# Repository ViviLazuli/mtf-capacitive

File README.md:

# MtF122 Capacitive Conversion PCB for IBM Model M 122-key Keyboards

### Rev. 2 / Rev. B

This version is in prototyping phase. However, it does function.

It has only been tested with a late thin-bezeled variant of the M122. The screw holes have a tight fit and may require widening and more clearance around them for traces.
!The screw holes may not be in the correct positions for other M122 variants!

Capacitive pad measurements are taken from i$/idollar's FSSK and FEXT PCB designs, which I believe are directly measured from the original Model F PCBs.

The PCB thickness should be 0.6mm. This is thin enough to allow the board to flex into shape without preforming it with heat and duct tape (which I couldn't make work anyway).

Standard glossy soldermask is probably the best choice. JLCPCB has had issues with wear on their black soldermask before. They have changed the formula, but a standard green/red/blue/yellow/purple/white/etc. glossy solder mask is probaby the safest bet for keyswitch wear resistance.
Higher wear resistance might also be achieved by coating the front of the capacitive pads in silkscreen, as silkscreen is an extra layer of epoxy. I am unsure how this will affect keyfeel or actuation, however.

There is a bullseye circle on the front of the board. This is for drilling a hole for a trackpoint module. There are redundant traces to allow for safer drilling at this location, but this functionality has not been tested!

The diameter of the copper around the connecting pads could be to be enlarged. They are too fragile and I had one rip out when disconnecting a mill-max pin header connector (fortunately it was just a redundant ground).

For connecting the board to an xwhatsit or other controller, I would recommend 3M 8132/06 100, which has the correct pitch for this board and xwhatsit:
https://www.digikey.com/en/products/detail/3m/8132-06-100/7809902

The key matrix of the PCB is reverse-engineered from photos of original F122 PCBs and should be exactly the same. The connector is likely in a slightly different position though.

The screw hole placement was prototyped with paper by printing an SVG output of the board edge cuts and drill holes on multiple sheets of paper, pasting them together, cutting out the paper 'PCB', and hole punching the drill hole locations. A few iterations of this paper prototyping method allowed me to test hole locations and board fitment against the barrel plate without having to make an entire PCB first.

I did not clad the steel backplate in tape before mounting the PCB. The solder mask should provide adequate isolation. Just make sure the steel is clean and there are no burrs/jagged edges that could scrape the PCB.

Please read LICENSE.txt for the full MIT License.

Some photos are here for reverse-engineering reference only and are not mine nor included under the license.

| Authors |
|-|
| ViviLazuli |
| Razerban |

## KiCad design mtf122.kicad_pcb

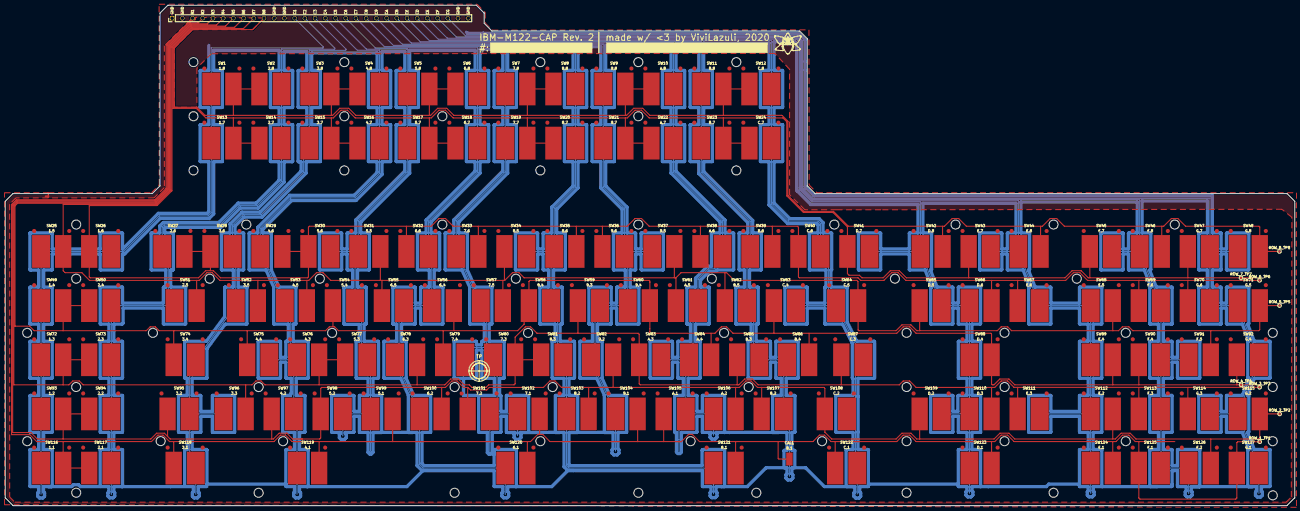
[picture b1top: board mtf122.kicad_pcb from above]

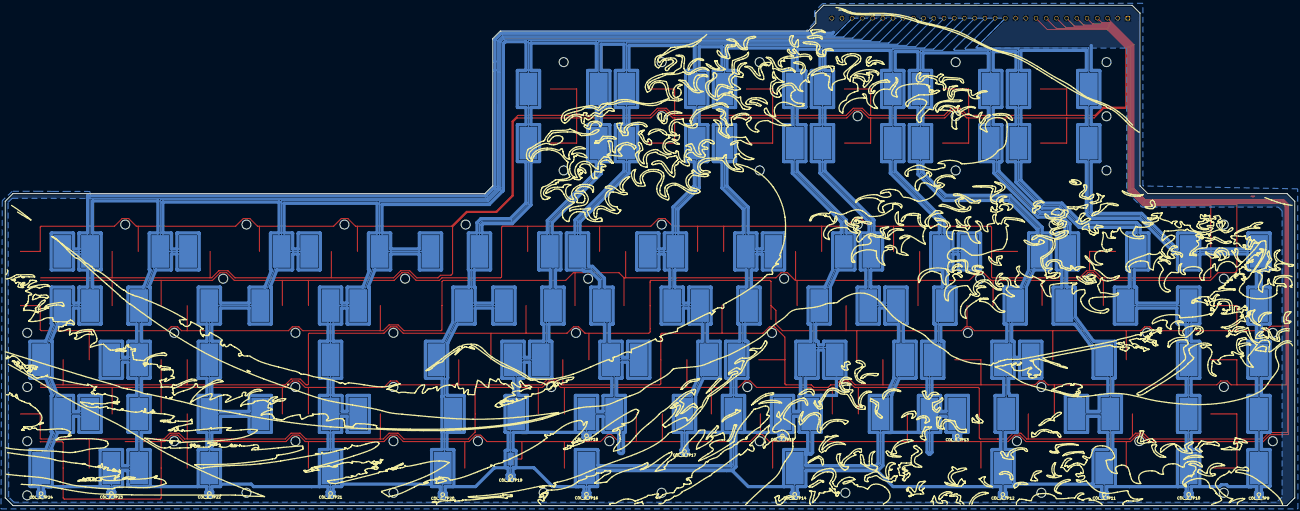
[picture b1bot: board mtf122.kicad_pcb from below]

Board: 2 copper layers, 500.0 x 194.0 mm, 216 parts (16 on the bottom side), 25 nets.

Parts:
CAL1: B,1; CAL_CAP_IBM_F
COL_1_TP9: C1_TestPoint; TestPoint_Pad_D1.0mm
COL_2_TP10: C2_TestPoint; TestPoint_Pad_D1.0mm
COL_3_TP11: C3_TestPoint; TestPoint_Pad_D1.0mm
COL_4_TP12: C4_TestPoint; TestPoint_Pad_D1.0mm
COL_5_TP13: C5_TestPoint; TestPoint_Pad_D1.0mm
COL_6_TP14: C6_TestPoint; TestPoint_Pad_D1.0mm
COL_7_TP15: C7_TestPoint; TestPoint_Pad_D1.0mm
COL_8_TP16: C8_TestPoint; TestPoint_Pad_D1.0mm
COL_9_TP17: C9_TestPoint; TestPoint_Pad_D1.0mm
COL_A_TP18: CA_TestPoint; TestPoint_Pad_D1.0mm
COL_B_TP19: CB_TestPoint; TestPoint_Pad_D1.0mm
COL_C_TP20: CC_TestPoint; TestPoint_Pad_D1.0mm
COL_D_TP21: CD_TestPoint; TestPoint_Pad_D1.0mm
COL_E_TP22: CE_TestPoint; TestPoint_Pad_D1.0mm
COL_F_TP23: CF_TestPoint; TestPoint_Pad_D1.0mm
COL_G_TP24: CG_TestPoint; TestPoint_Pad_D1.0mm
H1, H2, H3, H4, H5, H6, H7, H8, H9, H10, H11, H12, H13, H14, H15, H16, H17, H18, H19, H20, H21, H22, H23, H24, H25, H26, H27, H28, H29, H30, H31, H32, H33, H34, H35, H36, H37, H38, H39, H40, H41, H42, H43, H44, H45, H46, H47, H48, H49, H50, H51, H52, H53, H54, H55, H56, H57, H58, H59, H60, H61, H62, H63: HOLE
J1: CONN_CAP_IBM_F
ROW_1_TP1: R1_TestPoint; TestPoint_Pad_D1.0mm
ROW_2_TP2: R2_TestPoint; TestPoint_Pad_D1.0mm
ROW_3_TP3: R3_TestPoint; TestPoint_Pad_D1.0mm
ROW_4_TP4: R4_TestPoint; TestPoint_Pad_D1.0mm
ROW_5_TP5: R5_TestPoint; TestPoint_Pad_D1.0mm
ROW_6_TP6: R6_TestPoint; TestPoint_Pad_D1.0mm
ROW_7_TP7: R7_TestPoint; TestPoint_Pad_D1.0mm
ROW_8_TP8: R8_TestPoint; TestPoint_Pad_D1.0mm
SW1: 1,8; SW_CAP_IBM_F_ALT
SW2: 2,8; SW_CAP_IBM_F
SW3: 3,8; SW_CAP_IBM_F_ALT
SW4: 4,8; SW_CAP_IBM_F
SW5: 5,8; SW_CAP_IBM_F_ALT
SW6: 6,8; SW_CAP_IBM_F
SW7: 7,8; SW_CAP_IBM_F_ALT
SW8: 8,8; SW_CAP_IBM_F
SW9: 9,8; SW_CAP_IBM_F_ALT
SW10: A,8; SW_CAP_IBM_F
SW11: B,8; SW_CAP_IBM_F_ALT
SW12: C,8; SW_CAP_IBM_F
SW13: 1,7; SW_CAP_IBM_F_ALT
SW14: 2,7; SW_CAP_IBM_F
SW15: 3,7; SW_CAP_IBM_F_ALT
SW16: 4,7; SW_CAP_IBM_F
SW17: 5,7; SW_CAP_IBM_F_ALT
SW18: 6,7; SW_CAP_IBM_F
SW19: 7,7; SW_CAP_IBM_F_ALT
SW20: 8,7; SW_CAP_IBM_F
SW21: 9,7; SW_CAP_IBM_F_ALT
SW22: A,7; SW_CAP_IBM_F
SW23: B,7; SW_CAP_IBM_F_ALT
SW24: C,7; SW_CAP_IBM_F
SW25: 1,5; SW_CAP_IBM_F_ALT
SW26: 1,6; SW_CAP_IBM_F
SW27: 2,6; SW_CAP_IBM_F_ALT
SW28: 3,6; SW_CAP_IBM_F
SW29: 4,6; SW_CAP_IBM_F_ALT
SW30: 5,6; SW_CAP_IBM_F
SW31: 5,5; SW_CAP_IBM_F_ALT
SW32: 6,6; SW_CAP_IBM_F
SW33: 7,6; SW_CAP_IBM_F_ALT
SW34: 8,5; SW_CAP_IBM_F
SW35: 8,6; SW_CAP_IBM_F_ALT
SW36: 9,6; SW_CAP_IBM_F
SW37: 9,5; SW_CAP_IBM_F_ALT
SW38: A,6; SW_CAP_IBM_F
SW39: B,6; SW_CAP_IBM_F_ALT
SW40: C,6; SW_CAP_IBM_F
SW41: D,7; SW_CAP_IBM_F
SW42: D,8; SW_CAP_IBM_F_ALT
SW43: E,7; SW_CAP_IBM_F
SW44: E,8; SW_CAP_IBM_F_ALT
SW45: F,7; SW_CAP_IBM_F
SW46: F,8; SW_CAP_IBM_F_ALT
SW47: G,7; SW_CAP_IBM_F
SW48: G,8; SW_CAP_IBM_F_ALT
SW49: 1,4; SW_CAP_IBM_F_ALT
SW50: 2,4; SW_CAP_IBM_F
SW51: 2,5; SW_CAP_IBM_F_ALT
SW52: 3,5; SW_CAP_IBM_F_ALT
SW53: 4,5; SW_CAP_IBM_F_ALT
SW54: 5,4; SW_CAP_IBM_F
SW55: 6,5; SW_CAP_IBM_F
SW56: 6,4; SW_CAP_IBM_F_ALT
SW57: 7,5; SW_CAP_IBM_F_ALT
SW58: 8,4; SW_CAP_IBM_F
SW59: 9,3; SW_CAP_IBM_F
SW60: 9,4; SW_CAP_IBM_F_ALT
SW61: A,5; SW_CAP_IBM_F
SW62: B,5; SW_CAP_IBM_F
SW63: C,4; SW_CAP_IBM_F
SW64: C,5; SW_CAP_IBM_F_ALT
SW65: D,5; SW_CAP_IBM_F
SW66: D,6; SW_CAP_IBM_F_ALT
SW67: E,6; SW_CAP_IBM_F
SW68: E,5; SW_CAP_IBM_F_ALT
SW69: F,6; SW_CAP_IBM_F
SW70: G,6; SW_CAP_IBM_F
SW71: G,5; SW_CAP_IBM_F_ALT
SW72: 1,3; SW_CAP_IBM_F_ALT
SW73: 2,3; SW_CAP_IBM_F
SW74: 3,4; SW_CAP_IBM_F
SW75: 4,4; SW_CAP_IBM_F
SW76: 4,3; SW_CAP_IBM_F_ALT
SW77: 5,3; SW_CAP_IBM_F
SW78: 6,3; SW_CAP_IBM_F_ALT
SW79: 7,4; SW_CAP_IBM_F
SW80: 7,3; SW_CAP_IBM_F_ALT
SW81: 8,3; SW_CAP_IBM_F
SW82: 9,2; SW_CAP_IBM_F_ALT
SW83: A,3; SW_CAP_IBM_F
SW84: A,4; SW_CAP_IBM_F_ALT
SW85: B,3; SW_CAP_IBM_F
SW86: B,4; SW_CAP_IBM_F_ALT
SW87: C,3; SW_CAP_IBM_F
SW88: D,4; SW_CAP_IBM_F_ALT
SW89: E,4; SW_CAP_IBM_F_ALT
SW90: F,4; SW_CAP_IBM_F
SW91: F,5; SW_CAP_IBM_F_ALT
SW92: G,4; SW_CAP_IBM_F
SW93: 1,2; SW_CAP_IBM_F_ALT
SW94: 2,2; SW_CAP_IBM_F
SW95: 3,2; SW_CAP_IBM_F
SW96: 3,3; SW_CAP_IBM_F_ALT
SW97: 4,2; SW_CAP_IBM_F
SW98: 5,2; SW_CAP_IBM_F
SW99: 5,1; SW_CAP_IBM_F_ALT
SW100: 6,2; SW_CAP_IBM_F_ALT
SW101: 7,2; SW_CAP_IBM_F
SW102: 7,1; SW_CAP_IBM_F_ALT
SW103: 8,2; SW_CAP_IBM_F_ALT
SW104: 9,1; SW_CAP_IBM_F_ALT
SW105: A,1; SW_CAP_IBM_F
SW106: A,2; SW_CAP_IBM_F_ALT
SW107: B,2; SW_CAP_IBM_F
SW108: C,2; SW_CAP_IBM_F
SW109: D,2; SW_CAP_IBM_F
SW110: D,3; SW_CAP_IBM_F_ALT
SW111: E,3; SW_CAP_IBM_F
SW112: E,2; SW_CAP_IBM_F_ALT
SW113: F,3; SW_CAP_IBM_F
SW114: G,3; SW_CAP_IBM_F
SW115: G,2; SW_CAP_IBM_F_ALT
SW116: 1,1; SW_CAP_IBM_F_ALT
SW117: 2,1; SW_CAP_IBM_F
SW118: 3,1; SW_CAP_IBM_F
SW119: 4,1; SW_CAP_IBM_F_ALT
SW120: 6,1; SW_CAP_IBM_F_ALT
SW121: 8,1; SW_CAP_IBM_F_ALT
SW122: C,1; SW_CAP_IBM_F
SW123: D,1; SW_CAP_IBM_F_ALT
SW124: E,1; SW_CAP_IBM_F_ALT
SW125: F,1; SW_CAP_IBM_F
SW126: F,2; SW_CAP_IBM_F_ALT
SW127: G,1; SW_CAP_IBM_F

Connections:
COL_1: COL_1_TP9.1, J1.13, SW1.COL, SW13.COL, SW25.COL, SW26.COL, SW49.COL, SW72.COL, SW93.COL, SW116.COL
COL_2: COL_2_TP10.1, J1.14, SW2.COL, SW14.COL, SW27.COL, SW50.COL, SW51.COL, SW73.COL, SW94.COL, SW117.COL
COL_3: COL_3_TP11.1, J1.15, SW3.COL, SW15.COL, SW28.COL, SW52.COL, SW74.COL, SW95.COL, SW96.COL, SW118.COL
COL_4: COL_4_TP12.1, J1.16, SW4.COL, SW16.COL, SW29.COL, SW53.COL, SW75.COL, SW76.COL, SW97.COL, SW119.COL
COL_5: COL_5_TP13.1, J1.17, SW5.COL, SW17.COL, SW30.COL, SW31.COL, SW54.COL, SW77.COL, SW98.COL, SW99.COL
COL_6: COL_6_TP14.1, J1.18, SW6.COL, SW18.COL, SW32.COL, SW55.COL, SW56.COL, SW78.COL, SW100.COL, SW120.COL
COL_7: COL_7_TP15.1, J1.19, SW7.COL, SW19.COL, SW33.COL, SW57.COL, SW79.COL, SW80.COL, SW101.COL, SW102.COL
COL_8: COL_8_TP16.1, J1.20, SW8.COL, SW20.COL, SW34.COL, SW35.COL, SW58.COL, SW81.COL, SW103.COL, SW121.COL
COL_9: COL_9_TP17.1, J1.21, SW9.COL, SW21.COL, SW36.COL, SW37.COL, SW59.COL, SW60.COL, SW82.COL, SW104.COL
COL_A: COL_A_TP18.1, J1.22, SW10.COL, SW22.COL, SW38.COL, SW61.COL, SW83.COL, SW84.COL, SW105.COL, SW106.COL
COL_B: CAL1.COL, COL_B_TP19.1, J1.23, SW11.COL, SW23.COL, SW39.COL, SW62.COL, SW85.COL, SW86.COL, SW107.COL
COL_C: COL_C_TP20.1, J1.24, SW12.COL, SW24.COL, SW40.COL, SW63.COL, SW64.COL, SW87.COL, SW108.COL, SW122.COL
COL_D: COL_D_TP21.1, J1.25, SW41.COL, SW42.COL, SW65.COL, SW66.COL, SW88.COL, SW109.COL, SW110.COL, SW123.COL
COL_E: COL_E_TP22.1, J1.26, SW43.COL, SW44.COL, SW67.COL, SW68.COL, SW89.COL, SW111.COL, SW112.COL, SW124.COL
COL_F: COL_F_TP23.1, J1.27, SW45.COL, SW46.COL, SW69.COL, SW90.COL, SW91.COL, SW113.COL, SW125.COL, SW126.COL
COL_G: COL_G_TP24.1, J1.28, SW47.COL, SW48.COL, SW70.COL, SW71.COL, SW92.COL, SW114.COL, SW115.COL, SW127.COL
GND: J1.1, J1.2, J1.11, J1.12, J1.29, J1.30
ROW_1: CAL1.ROW, J1.3, ROW_1_TP1.1, SW99.ROW, SW102.ROW, SW104.ROW, SW105.ROW, SW116.ROW, SW117.ROW, SW118.ROW, SW119.ROW, SW120.ROW, SW121.ROW, SW122.ROW, SW123.ROW, SW124.ROW, SW125.ROW, SW127.ROW
ROW_2: J1.4, ROW_2_TP2.1, SW82.ROW, SW93.ROW, SW94.ROW, SW95.ROW, SW97.ROW, SW98.ROW, SW100.ROW, SW101.ROW, SW103.ROW, SW106.ROW, SW107.ROW, SW108.ROW, SW109.ROW, SW112.ROW, SW115.ROW, SW126.ROW
ROW_3: J1.5, ROW_3_TP3.1, SW59.ROW, SW72.ROW, SW73.ROW, SW76.ROW, SW77.ROW, SW78.ROW, SW80.ROW, SW81.ROW, SW83.ROW, SW85.ROW, SW87.ROW, SW96.ROW, SW110.ROW, SW111.ROW, SW113.ROW, SW114.ROW
ROW_4: J1.6, ROW_4_TP4.1, SW49.ROW, SW50.ROW, SW54.ROW, SW56.ROW, SW58.ROW, SW60.ROW, SW63.ROW, SW74.ROW, SW75.ROW, SW79.ROW, SW84.ROW, SW86.ROW, SW88.ROW, SW89.ROW, SW90.ROW, SW92.ROW
ROW_5: J1.7, ROW_5_TP5.1, SW25.ROW, SW31.ROW, SW34.ROW, SW37.ROW, SW51.ROW, SW52.ROW, SW53.ROW, SW55.ROW, SW57.ROW, SW61.ROW, SW62.ROW, SW64.ROW, SW65.ROW, SW68.ROW, SW71.ROW, SW91.ROW
ROW_6: J1.8, ROW_6_TP6.1, SW26.ROW, SW27.ROW, SW28.ROW, SW29.ROW, SW30.ROW, SW32.ROW, SW33.ROW, SW35.ROW, SW36.ROW, SW38.ROW, SW39.ROW, SW40.ROW, SW66.ROW, SW67.ROW, SW69.ROW, SW70.ROW
ROW_7: J1.9, ROW_7_TP7.1, SW13.ROW, SW14.ROW, SW15.ROW, SW16.ROW, SW17.ROW, SW18.ROW, SW19.ROW, SW20.ROW, SW21.ROW, SW22.ROW, SW23.ROW, SW24.ROW, SW41.ROW, SW43.ROW, SW45.ROW, SW47.ROW
ROW_8: J1.10, ROW_8_TP8.1, SW1.ROW, SW2.ROW, SW3.ROW, SW4.ROW, SW5.ROW, SW6.ROW, SW7.ROW, SW8.ROW, SW9.ROW, SW10.ROW, SW11.ROW, SW12.ROW, SW42.ROW, SW44.ROW, SW46.ROW, SW48.ROW

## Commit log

2021-01-23 initial publishing - VERY WIP
2021-02-01 Update CONN_CAP_IBM_F footprint
2021-02-01 Updated SW_CAP_IBM_F and SW_CAP_IBM_F_ALT footprints
2021-02-01 Added extra appendages to be compliant with IBM rules
2021-02-01 Added test points for testing continuity on ROWS
2021-02-01 Added test points for testing continuity on COLUMNS
2021-02-01 1- Resized the top edge of the PCB to fit inside the keyboard without any permanent irreversable modification. 2- Routed the connections to take less space 3- Added a GND fill zone on the back of the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
2021-02-01 Some cleaning
2021-02-01 Removed column test points from F.SilkS
2021-02-25 Cleanup and schematic update
2021-04-07 typo
